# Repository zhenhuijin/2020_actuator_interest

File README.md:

# 2020_actuator_interest
带通讯电热执行器+box

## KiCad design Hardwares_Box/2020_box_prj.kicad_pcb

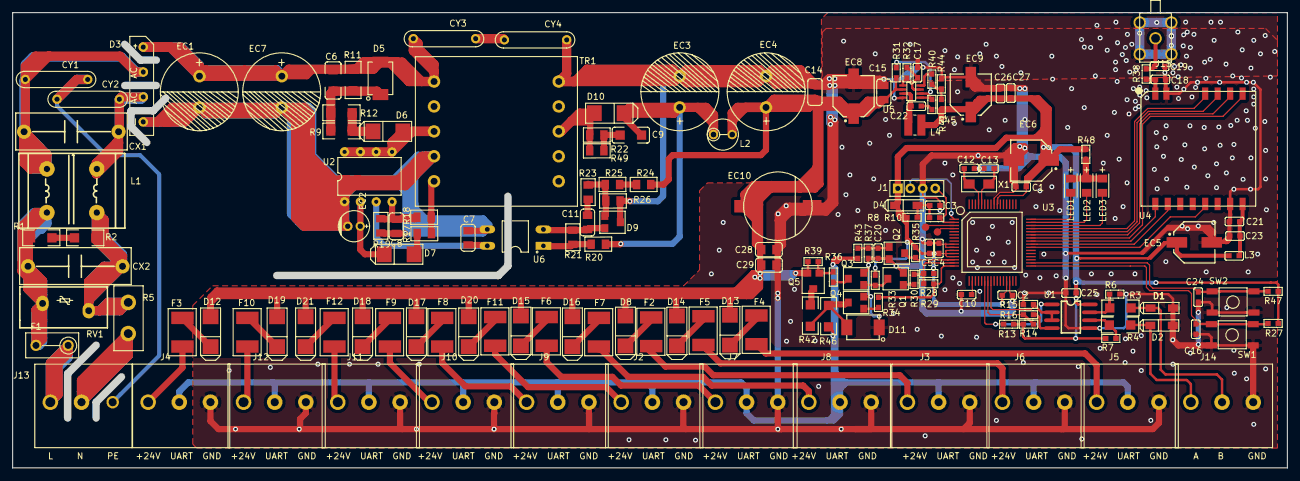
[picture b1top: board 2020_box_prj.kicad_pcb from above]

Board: 2 copper layers, 203.3 x 71.9 mm, 167 parts (0 on the bottom side), 104 nets.

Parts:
C1: 1uF_0603; CAP.SMT.0603C
C2, C3, C4, C10, C25: 0.1uF_0603; CAP.SMT.0603C
C5: 10uF_0603; CAP.SMT.0603C
C6: 2.2nF.1kv; CAP.SMT.1206C
C7: 1nF.0805; CAP.SMT.0805C
C8: 10pF.0805; CAP.SMT.0805C
C9: 1nF.630V; CAP.SMT.1206C
C11, C14, C15: 100nF.0805; CAP.SMT.0805C
C12, C13: 12pF/0603; CAP.SMT.0603C
C16, C17, C24: 1nF_0603; CAP.SMT.0603C
C18, C19: NC; CAP.SMT.0603C
C20: 51pF_0603; CAP.SMT.0603C
C21: 10nF.0603; CAP.SMT.0603C
C22: 0.1uF/0603; CAP.SMT.0603C
C23: 1uF.0603; CAP.SMT.0603C
C26: 1uF/0603; CAP.SMT.0603C
C27: 10nF/0603; CAP.SMT.0603C
C28: 1uF.0805; CAP.SMT.0805C
C29: 0.1uF.0805; CAP.SMT.0805C
CX1: 0.22uF.275V; CAP.DIP.X.0.15uF／275V
CX2: 0.1uF.275V; CAP.DIP.X.0.15uF／275V
CY1, CY2: 102M250V; CAP.DIP.Y.102M／250V
CY3, CY4: 222M250V; CAP.DIP.Y.102M／250V
D1, D2: SMBJ6.5A; D.SMT.SOD-123
D3: KBP310; D.SMT.KBP310G
D4: 1N4148; D.SMT.1N4148.SOD-123
D5: SMBJ180A; D.SMT.SMBJ6.5A.D0-214
D6: FFM107.D0-214; D.SMT.1N5819.SMA
D7: FFM107; D.SMT.1N5819.SMA
D8, D12, D13, D14, D15, D16, D17, D18, D19, D20, D21: 1N5819; D.SMT.1N5819.SMA
D9: D.SMT.MMTL431A; BJT.SMT.SOT-23
D10: SK520; D.SMT.1N5819.SMA
D11: SMBJ28CA; D.SMT.SMBJ6.5A.D0-214
EC1, EC7: 33uF.400V; CAP.DIP.680uF50V 12.5X20
EC2: 10uF.50V; CAP.DIP.10uF／50V.5.2X11.6
EC3, EC4: 680uF.50V; CAP.DIP.680uF50V 12.5X20
EC5, EC6, EC9: 220uF.16V; CAP.SMT.220UF.16V
EC8: 220uF.50V; CAP.SMT.220UF.16V
EC10: 220uF.50V; CAP.SMT.220uF.50V
F1: FUSE_DIP_3.15A; FUSE.3.15A
F2, F3, F4, F5, F6, F7, F8, F9, F10, F11, F12: 500MA; FUSE.100MA.SMC
J1: CON-1x4PIN-2.0MM; CON_DIP_1X4PIN_2.0MM
J2, J3, J4, J5, J6, J7, J8, J9, J10, J11, J12, J13, J14: CON-1x3PIN-3.5MM; CON_DIP_1X3PIN_5.0MM_WJ103
J15: ANT_SMA; OTHER.SMA
L1: UU9.8 20mH 1A; L.DIP.UU9.8
L2: 3.3uH 5A; L.PID.2.2mH
L3: 10uH; CAP.SMT.0603C
L4: 10uH; L.SMT.3010
LED1, LED2, LED3: HG635A-TRB; D.BL-HG635A-TRB-LED
Q1, Q2, Q3, Q4: BC817; BJT.SMT.SOT-23
Q5: BC807; BJT.SMT.SOT-23
R1, R2: 2M.1206; RES.SMT.1206
R3, R4: 10R.1206; RES.SMT.1206
R5: NTC.5D-13; FUSE.DIP.10D-9
R6, R7, R13, R14, R15: 10K.0603; RES.SMT.0603
R8, R27, R47: 47K/0603; RES.SMT.0603
R9, R12: 200R.1206; RES.SMT.1206
R10: 430R/0603; RES.SMT.0603
R11: 150K.2W; RES.SMT.1210
R16: 100R.0603; RES.SMT.0603
R17: 6R8.0805; RES.SMT.0805
R18: 43k.0805; RES.SMT.0805
R19: 6.8k.0805; RES.SMT.0805
R20: 1.8K.0805; RES.SMT.0805
R21: 1K.0805; RES.SMT.0805
R22, R49: 47R.0805; RES.SMT.0805
R23: 4.7K.0805; RES.SMT.0805
R24: 30K.0805; RES.SMT.0805
R25: 56K.0805; RES.SMT.0805
R26: 10K.0805; RES.SMT.0805
R28, R29, R30, R32, R33, R35, R36, R39: 10K/0603; RES.SMT.0603
R31: 100K/0603; RES.SMT.0603
R34, R37, R48: 1K/0603; RES.SMT.0603
R38: 0R.0603; RES.SMT.0603
R40: 33K/0603; RES.SMT.0603
R41: 20R/0603; RES.SMT.0603
R42, R46: 100R/1206; RES.SMT.1206
R43: 4.7K/0603; RES.SMT.0603
R44: 12K/0603; RES.SMT.0603
R45: 39K/0603; RES.SMT.0603
RV1: TDK471KD14; RES.DIP.RV.TDK471KD14
SW1, SW2: SW.SMT.E51.6x6x4.3; SWITCH_KAN4542
T1, T2: TSET; OTHER.TEST
TR1: EF25_25W_PN8160J; L_TRANS_DIP_EF25_PN8160_25W
U1: MS1585; IC.SMT.SOIC-8
U2: PN8160J.DIP-8; IC_DIP-8
U3: MCU-STM8L052R8T6; MCU.LQFP.64.10x10mm.0.5mm
U4: MOLDE.SMT.LSD4RF-2F717N30; Modle.LSD4RF.2F717N30
U5: MPS9942.SOT23-8; IC.SMT.SOT23-8
U6: OPTO_DIP_PC817B_DIP-4P; OPTO.DIP.PC817B
X1: OSC-32.768kHz; OSC.SMT.32.768KHz

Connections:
+3.3VA: C21.2, C23.1, L3.1, U4.8
+3V3: C1.1, C2.1, C4.1, C5.1, C25.1, C26.2, C27.2, D4.1, EC5.1, EC6.1, EC9.1, J1.1, L3.2, L4.1, R7.1, R8.2, R13.1, R14.1, R27.1, R28.1, R33.1, R35.1, R45.1, R47.2, R48.2, U1.8, U3.11, U3.12, U3.13, U3.29, U3.55
+24V: C14.1, C15.1, C28.1, C29.1, D8.2, D12.2, D13.2, D14.2, D15.2, D16.2, D17.2, D18.2, D19.2, D20.2, D21.2, EC4.1, EC8.1, EC10.1, L2.2, Q5.2, R24.1, R31.2, R39.1, U5.2
/CTRCL1: R29.2, R34.1, U3.16
/LINE: F1.2, J13.1
/NINE: J13.2, R5.2
/NRST: J1.4, R10.1, U3.2
/PE: CY1.1, CY2.2, J13.3
/RF_DIO0: U3.40, U4.2
/RF_DIO3: U3.39, U4.5
/RF_RST: U3.41, U4.1
/RF_RunLed: LED2.1, U3.47
/RF_SPI_CSN: U3.44, U4.11
/RF_SPI_SCLK: U3.45, U4.12
/RF_SPI_SI: U3.43, U4.10
/RF_SPI_SO: U3.42, U4.9
/RF_WIRE: C18.1, R38.2, U4.14
/RS485A: D2.1, J14.1, R4.1
/RS485B: D1.1, J14.2, R3.1
/RXD1: Q2.3, R35.2, U3.14
/RunLed: LED1.1, U3.48
/SW1: C16.2, R27.2, SW1.3, SW1.4, U3.33
/SW2: C24.2, R47.1, SW2.3, SW2.4, U3.34
/SWIM: J1.2, U3.1
/TXD1: R28.2, R29.1, R30.2, U3.15
/U2_EN: R15.2, U1.2, U1.3, U3.24
/U2_RXD: R13.2, U1.1, U3.22
/U2_TXD: R14.2, R16.1, U3.23
/UART: J2.2, J3.2, J4.2, J5.2, J6.2, J7.2, J8.2, J9.2, J10.2, J11.2, J12.2, R43.2, R46.2
/Uart__RunLed: LED3.1, U3.46
GND: C1.2, C2.2, C3.2, C4.2, C5.2, C10.2, C12.2, C13.1, C14.2, C15.2, C16.1, C17.2, C18.2, C19.2, C20.2, C21.1, C23.2, C24.1, C25.2, C26.1, C27.1, C28.2, C29.2, CY4.1, D1.2, D2.2, D9.3, D11.1, EC3.2, EC4.2, EC5.2, EC6.2, EC8.2, EC9.2, EC10.2, J1.3, J2.3, J3.3, J4.3, J5.3, J6.3, J7.3, J8.3, J9.3, J10.3, J11.3, J12.3, J14.3, Q1.2, Q2.2, Q3.2, Q4.2, R6.1, R15.1, R26.2, R37.1, R44.2, SW1.1, SW1.2, SW2.1, SW2.2, TR1.10, U1.5, U3.9, U3.10, U3.30, U3.56, U4.7, U4.13, U5.4
GNDA: C7.2, C8.1, D3.4, EC1.2, EC2.2, EC7.2, R19.2, TR1.4, U2.1, U6.3
unnamed: C3.1, D4.2, R8.1, R10.2
unnamed: C6.1, CY3.2, D3.3, D5.2, EC1.1, EC7.1, R11.1, TR1.1
unnamed: C6.2, D5.1, R9.1, R11.2, R12.1
unnamed: C7.1, U2.3, U6.4
unnamed: C8.2, R18.2, R19.1, U2.4
unnamed: C9.1, D10.1, EC3.1, L2.1, R20.1
unnamed: C9.2, R22.2, R49.2
unnamed: C10.1, U3.18
unnamed: C11.1, R23.2
unnamed: C11.2, D9.2, R21.2, U6.2
unnamed: C12.1, U3.61, X1.1
unnamed: C13.2, U3.60, X1.2
unnamed: C17.1, R32.2, U5.7
unnamed: C19.1, J15.1, R38.1
unnamed: C20.1, Q2.1, R37.2, R43.1
unnamed: C22.1, R41.1
unnamed: C22.2, L4.2, U5.3
unnamed: CX1.1, CY2.1, D3.2, L1.2
unnamed: CX1.2, CY1.2, D3.1, L1.1
unnamed: CX2.1, L1.3, R2.1, R5.1, RV1.2
unnamed: CX2.2, F1.1, L1.4, R1.2, RV1.1
unnamed: CY3.1, CY4.2
unnamed: D6.1, R9.2, R12.2
unnamed: D6.2, TR1.3, U2.5, U2.6, U2.7, U2.8
unnamed: D7.1, EC2.1, U2.2
unnamed: D7.2, R17.1
unnamed: D8.1, F2.1
unnamed: D9.1, R23.1, R25.2, R26.1
unnamed: D10.2, R22.1, R49.1, TR1.8
unnamed: D11.2, Q4.3, R42.1, R46.1
unnamed: D12.1, F3.1
unnamed: D13.1, F4.1
unnamed: D14.1, F5.1
unnamed: D15.1, F6.1
unnamed: D16.1, F7.1
unnamed: D17.1, F8.1
unnamed: D18.1, F9.1
unnamed: D19.1, F10.1
unnamed: D20.1, F11.1
unnamed: D21.1, F12.1
unnamed: F2.2, J3.1
unnamed: F3.2, J4.1
unnamed: F4.2, J5.1
unnamed: F5.2, J6.1
unnamed: F6.2, J7.1
unnamed: F7.2, J8.1
unnamed: F8.2, J9.1
unnamed: F9.2, J10.1
unnamed: F10.2, J12.1
unnamed: F11.2, J2.1
unnamed: F12.2, J11.1
unnamed: LED1.2, LED2.2, LED3.2, R48.1
unnamed: Q1.1, R30.1
unnamed: Q1.3, Q3.1, R33.2
unnamed: Q3.3, R36.2
unnamed: Q4.1, R34.2
unnamed: Q5.1, R36.1, R39.2
unnamed: Q5.3, R42.2
unnamed: R1.1, R2.2
unnamed: R3.2, R6.2, U1.7
unnamed: R4.2, R7.2, U1.6
unnamed: R16.2, U1.4
unnamed: R17.2, R18.1, TR1.5
unnamed: R20.2, R21.1, U6.1
unnamed: R24.2, R25.1
unnamed: R31.1, U5.6
unnamed: R32.1, U5.1
unnamed: R40.1, R44.1, R45.2
unnamed: R40.2, U5.8
unnamed: R41.2, U5.5
unnamed: T1.1, U3.4
unnamed: T2.1, U3.3

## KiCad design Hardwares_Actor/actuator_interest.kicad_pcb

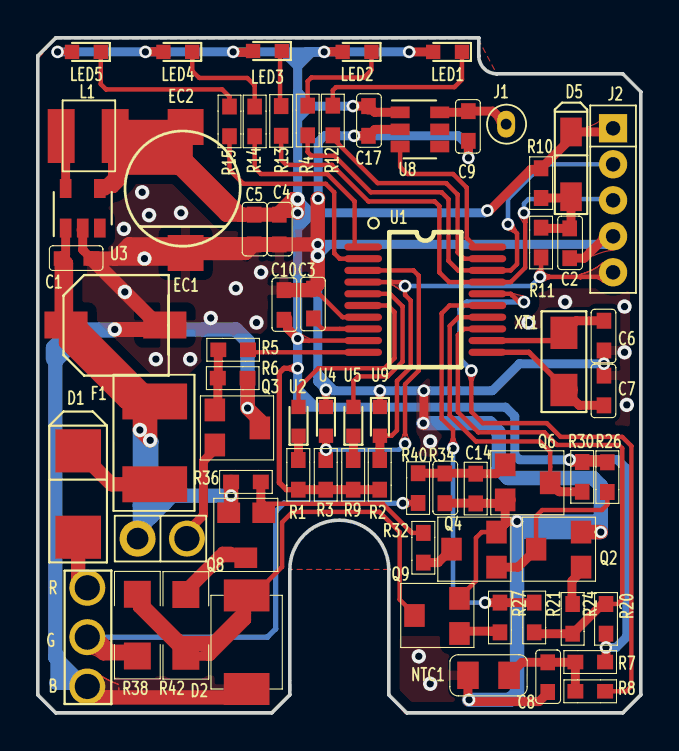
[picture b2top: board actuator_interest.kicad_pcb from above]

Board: 2 copper layers, 33.5 x 37.5 mm, 70 parts (0 on the bottom side), 45 nets.

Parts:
C1, C2, C5, C8, C17: 0.1uF_0603; CAP.SMT.0603C
C3: 4.7uF_0603; CAP.SMT.0603C
C4, C10: 1uF_0603; CAP.SMT.0603C
C6, C7, C9: 12pF_0603; CAP.SMT.0603C
C14: 51pF_0603; CAP.SMT.0603C
D1: 1N5819.D0-214; D.SMT.1N5819.SMA
D2: SMBJ28CA; D.SMT.SMBJ13CA.D0-214
D5: 1N4148; D.SMT.1N4148.SOD-123
EC1: 47uF.50V; CAP.SMT.47UF.25V
EC2: 100uF.10V; CAP.SMT.47UF.16V
F1: PTC_500MA; FUSE.100MA.SMC
J1: Touch; CON_DIP_1PIN_copy
J2: CON.DIP.1X5P.2.0MM; CON_DIP_1X5PIN_2.0MM
J3: CON.DIP.1X2P.2.54MM; CON_DIP_1X2PIN_2.54MM
L1: SWPA6045S470MT; L.SMT.SWPA3015S150MT
LED1, LED2, LED3, LED4, LED5: HUF34A-TRB-0805; D.LED.SMT.0603
NTC1: 3380(10K).0805; SENOR.SMT.NTC.0805
Q2, Q4, Q6: BJT_SS8050; BJT.SMT.SOT-23
Q3: AO3422_SOT23; BJT.SMT.SOT-23
Q8: BJT_BC807; BJT.SMT.SOT-23
Q9: BJT_BC817; BJT.SMT.SOT-23
R1, R4, R9, R12, R13, R14, R15, R27, R34: 1K/0603; RES.SMT.0603
R2, R3, R5, R6, R7, R10, R20, R21, R24, R26, R30, R32, R36: 10K/0603; RES.SMT.0603
R8, R11: 430R/0603; RES.SMT.0603
R38, R42: 100R/1206; RES.SMT.1206
R40: 4.7K/0603; RES.SMT.0603
U1: MCU.HC32L110C6PA.SOP-20; SOP-20
U2, U5: MPT6038C_3T_IR; D.LED.SMT.0603
U3: AP2307TB-A1.SOT23-5; IC.SMT.SOT-23-5
U4, U9: MPT60363T_IR; D.LED.SMT.0603
U8: BS812-1.SOT23-6; IC.SMT.SOT-23-6
U10: CON.1X3P5.0MM.WJ103; CON_DIP_3PIN_2.54MM
XT1: FC-135_32.768KHZ; OSC.SMT.32.768KHz

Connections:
+5V: C4.1, C5.1, C10.2, C17.1, D5.1, EC2.1, J2.1, L1.2, LED1.2, LED2.2, LED3.2, LED4.2, LED5.2, R1.1, R2.1, R3.1, R7.1, R9.1, R10.2, R20.1, R26.1, R30.1, U1.9, U3.4, U8.1
+24V: C1.1, EC1.1, F1.1, J3.1, Q8.2, R36.1, U3.1
/+24V1: D1.2, U10.1
/AD_InSide: R8.1, U1.16
/CTRCL1: R21.2, R27.1, U1.15
/IR1_Recieve: R3.2, U1.3, U4.2
/IR1_TX1: U1.6, U2.2
/IR2_Recieve: J2.5, R2.2, R11.1, U1.4, U9.2
/IR2_TX2: U1.5, U5.2
/Kout1: U1.20, U8.3
/LED_1MM: J2.2, R4.2, U1.18
/LED_2MM: J2.3, R13.2, U1.17
/LED_3MM: R14.2, U1.1
/LED_4MM: R15.2, U1.2
/O_Actuator: R5.2, U1.10
/RXD1: Q6.3, R30.2, U1.14
/Run_LED: R12.2, U1.19
/TXD1: R20.2, R21.1, R24.2, U1.13
/UART1: R40.2, R42.2, U10.2
GND: C1.2, C2.2, C3.2, C4.2, C5.2, C6.1, C7.2, C8.2, C9.1, C10.1, C14.2, C17.2, D2.1, EC1.2, EC2.2, J2.4, NTC1.1, Q2.2, Q3.3, Q4.2, Q6.2, Q9.2, R6.1, R34.1, U1.7, U3.2, U4.1, U8.2, U9.1, U10.3
unnamed: C2.1, D5.2, R10.1, R11.2
unnamed: C3.1, U1.8
unnamed: C6.2, U1.12, XT1.1
unnamed: C7.1, U1.11, XT1.2
unnamed: C8.1, NTC1.2, R7.2, R8.2
unnamed: C9.2, J1.1, U8.6
unnamed: C14.1, Q6.1, R34.2, R40.1
unnamed: D1.1, F1.2
unnamed: D2.2, Q9.3, R38.1, R42.1
unnamed: J3.2, Q3.2
unnamed: L1.1, U3.5
unnamed: LED1.1, R12.1
unnamed: LED2.1, R4.1
unnamed: LED3.1, R13.1
unnamed: LED4.1, R14.1
unnamed: LED5.1, R15.1
unnamed: Q2.1, R24.1
unnamed: Q2.3, Q4.1, R26.2
unnamed: Q3.1, R5.1, R6.2
unnamed: Q4.3, R32.2
unnamed: Q8.1, R32.1, R36.2
unnamed: Q8.3, R38.2
unnamed: Q9.1, R27.2
unnamed: R1.2, U2.1
unnamed: R9.2, U5.1

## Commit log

2020-10-08 上传文档资料
